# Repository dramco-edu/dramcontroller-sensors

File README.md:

# Dramcontroller Sensors
Description and hardware schemes for sensors compatible with dramcontroller boards

In academic year 2021-2022, students have access to six different sensor modules. 
- Button Sensor
- Capacitive Touch Sensor
- Sound Sensor
- Inertial Measurement Unit Sensor
- Digital Light Intensity Sensor
- Proximity Sensor

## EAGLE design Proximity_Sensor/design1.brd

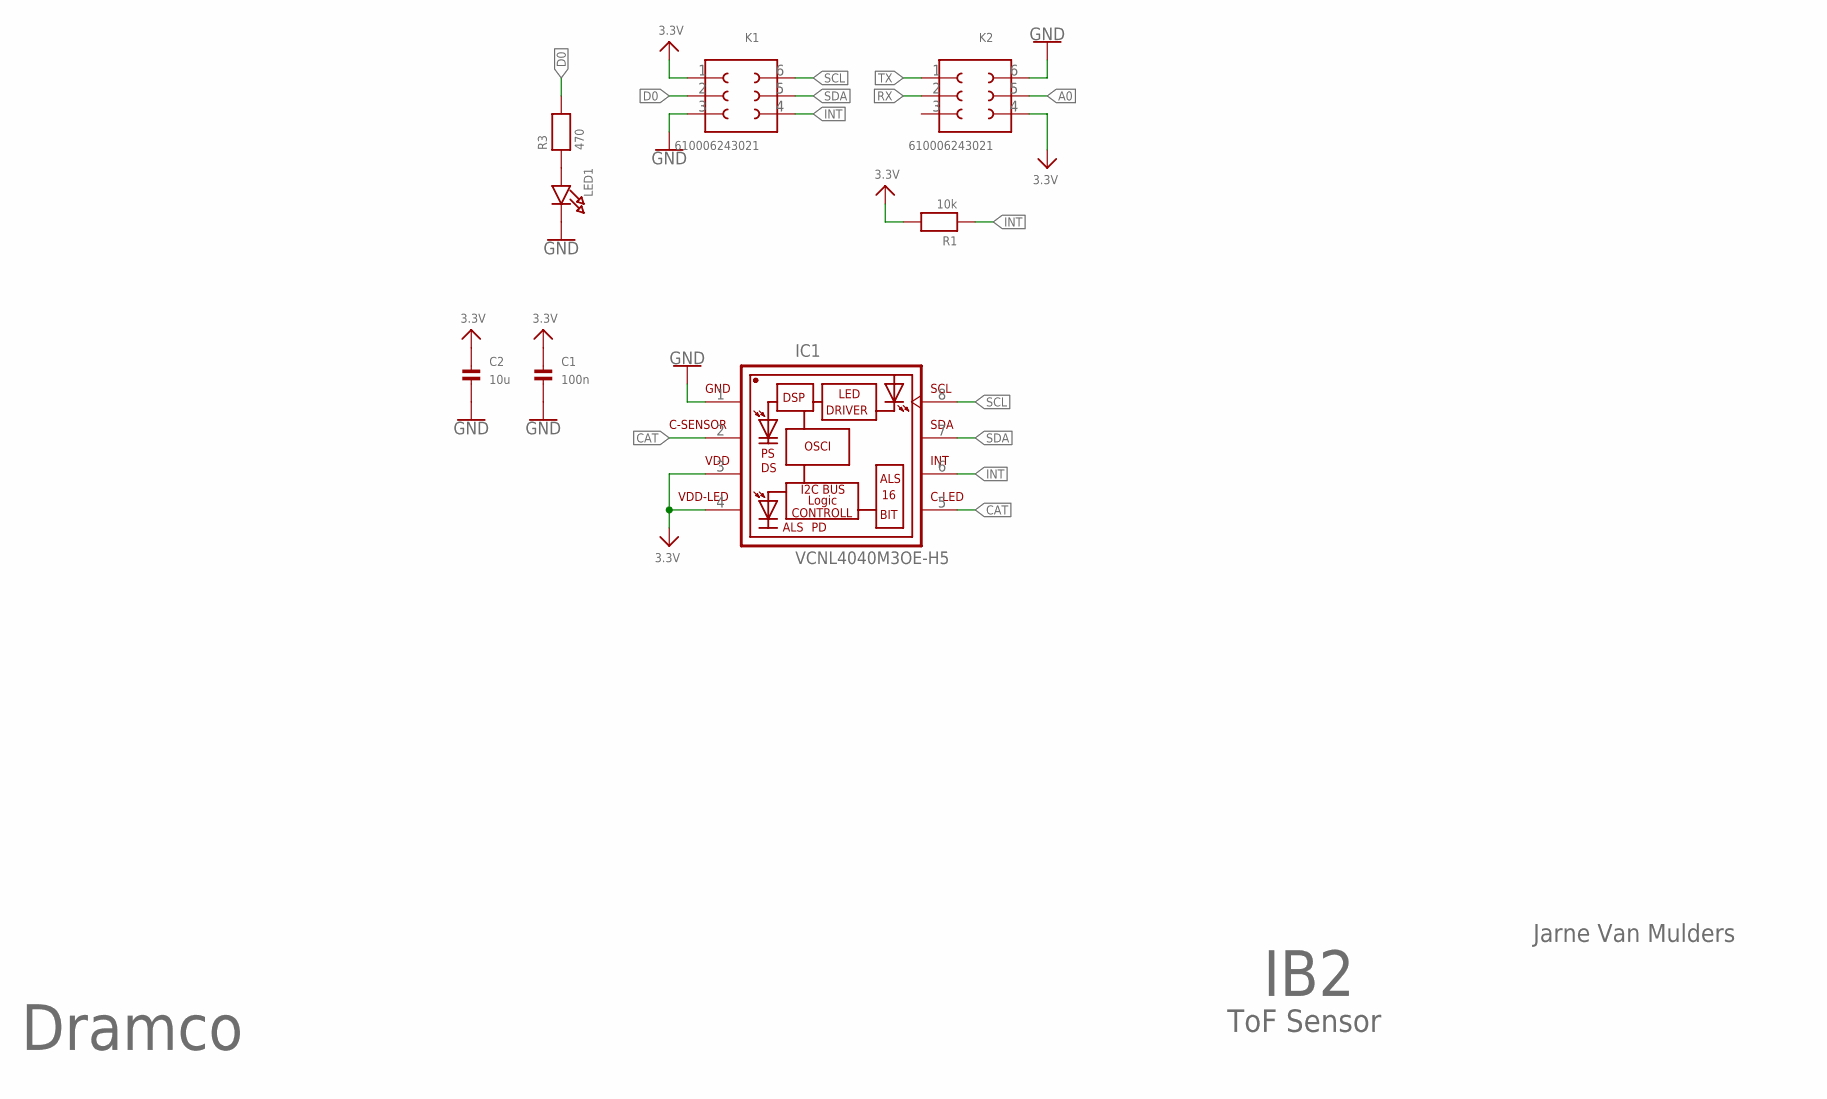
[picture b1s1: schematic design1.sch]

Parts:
C1: 100n; 0603
C2: 10u; 0805
IC1: VCNL4040M3OE-H5; VISHAY_VCNL4040_4.34X2.35X3.65
K1, K2: 610006243021
LED1: LED0805; CHIPLED_0805
R1: 10k; 0603
R3: 470; 0603

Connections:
3.3V: C1.1, C2.1, IC1.3 (VDD), IC1.4 (VDD-LED), K1.1, K2.4, R1.2
A0: K2.5
CAT: IC1.2 (C-SENSOR), IC1.5 (C-LED)
D0: K1.2, R3.2
GND: C1.2, C2.2, IC1.1 (GND), K1.3, K2.6, LED1.C
INT: IC1.6 (INT), K1.4, R1.1
unnamed: LED1.A, R3.1
RX: K2.2
SCL: IC1.8 (SCL), K1.6
SDA: IC1.7 (SDA), K1.5
TX: K2.1

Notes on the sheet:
Dramco
IB2
ToF Sensor
Jarne Van Mulders

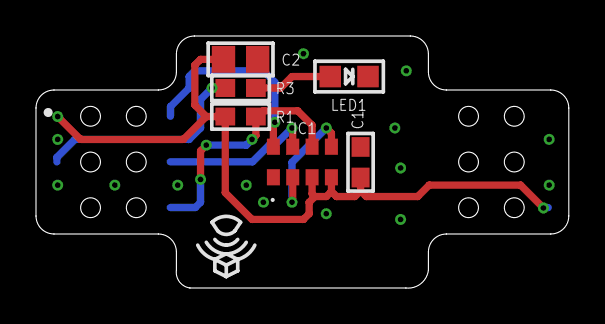
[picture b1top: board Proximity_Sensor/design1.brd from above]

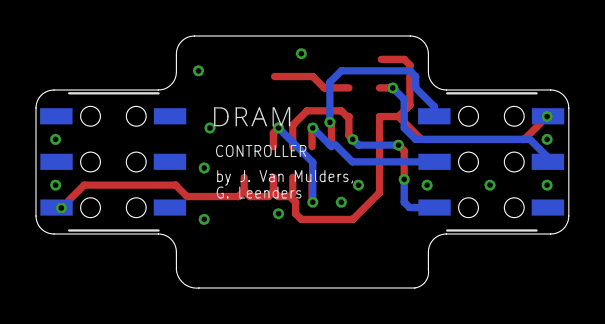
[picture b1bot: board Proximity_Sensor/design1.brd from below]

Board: 2 copper layers, 29.6 x 14.0 mm, 8 parts (2 on the bottom side), 8 nets.

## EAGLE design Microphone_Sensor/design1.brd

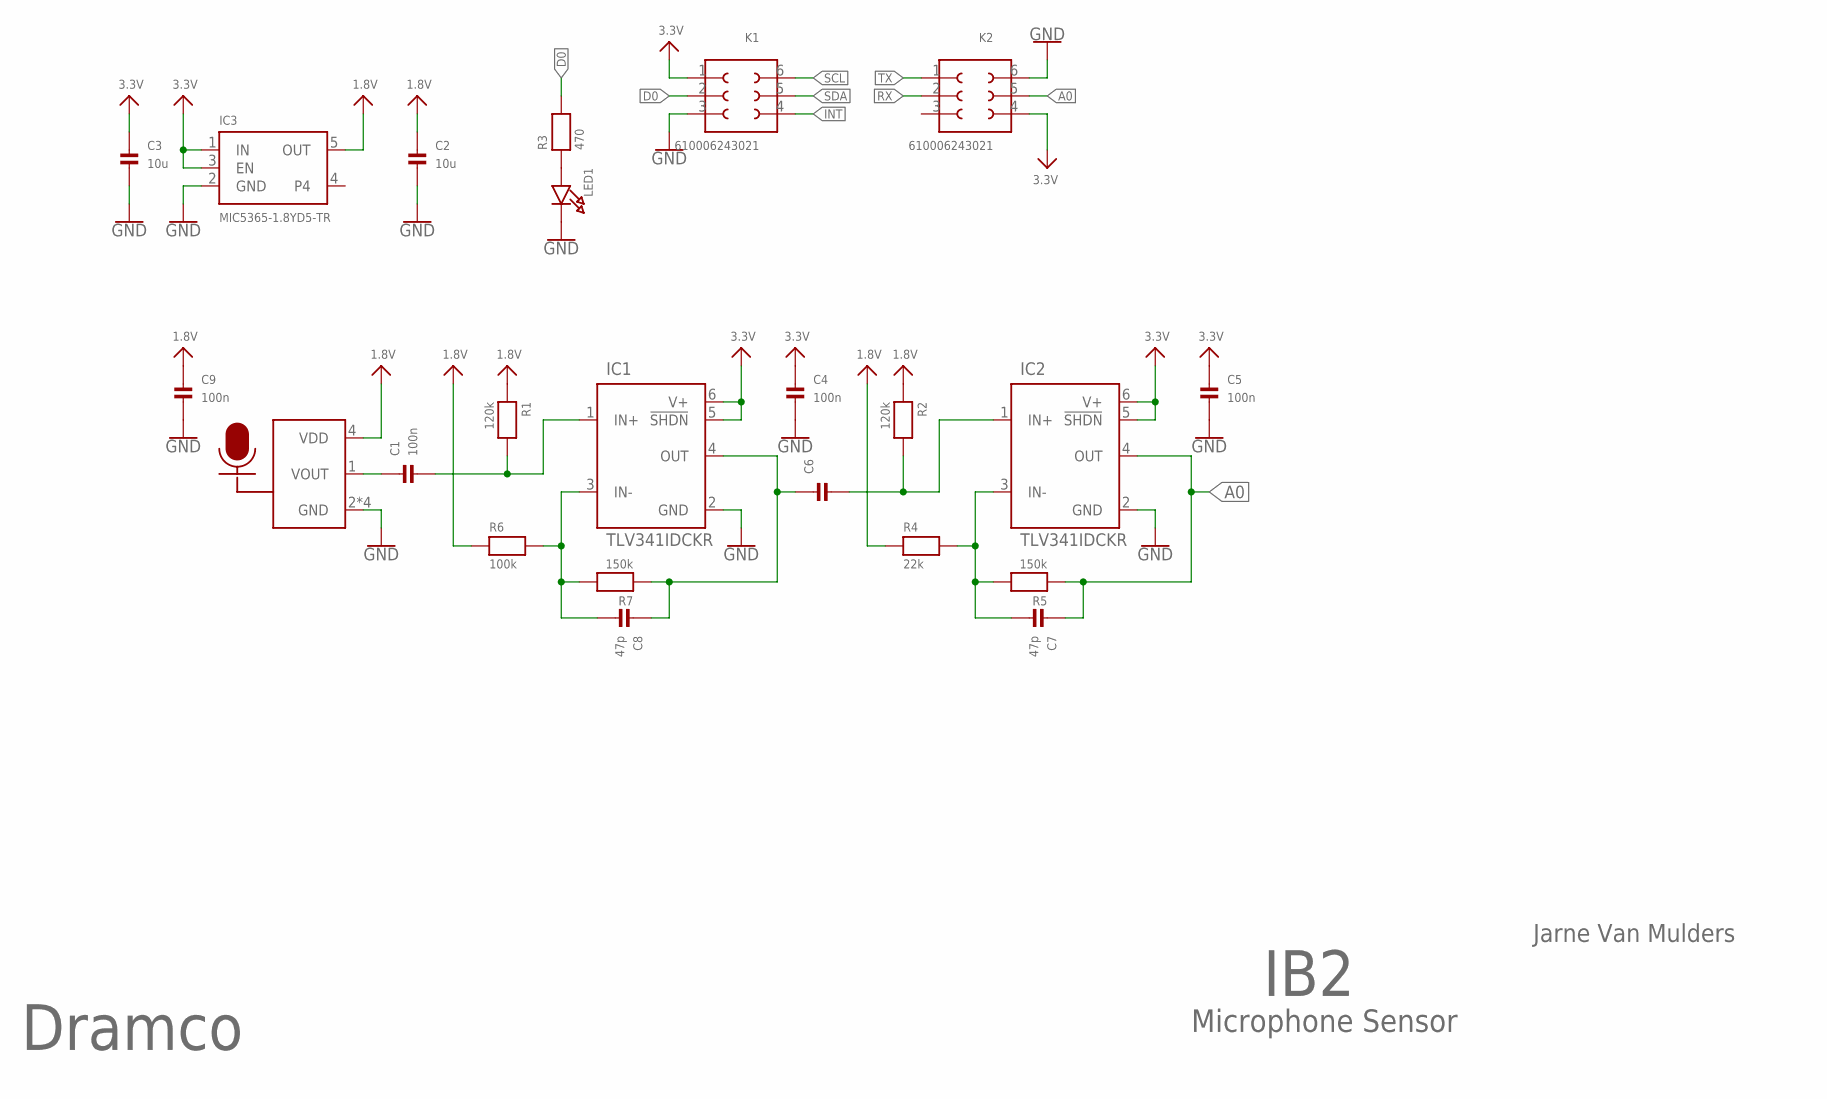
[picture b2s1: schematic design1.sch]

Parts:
C1, C4, C5, C9: 100n; 0603-MINI
C2, C3: 10u; 0603-MINI
C6: CAP_CERAMIC0603MINI; 0603-MINI
C7, C8: 47p; 0603-MINI
IC1, IC2: TLV341IDCKR; SOT65P210X110-6N
IC3: MIC5365-1.8YD5-TR; SOT23-5
IC4: VM1000
K1, K2: 610006243021
LED1: LED0805; CHIPLED_0805
R1, R2: 120k; 0603-MINI
R3: 470; 0603-MINI
R4: 22k; 0603-MINI
R5, R7: 150k; 0603-MINI
R6: 100k; 0603-MINI

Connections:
1.8V: C2.1, C9.1, IC3.5 (OUT), IC4.4 (VDD), R1.1, R2.1, R4.1, R6.1
3.3V: C3.1, C4.1, C5.1, IC1.5 (!SHDN!), IC1.6 (V+), IC2.5 (!SHDN!), IC2.6 (V+), IC3.1 (IN), IC3.3 (EN), K1.1, K2.4
A0: C7.1, IC2.4 (OUT), K2.5, R5.1
D0: K1.2, R3.2
GND: C2.2, C3.2, C4.2, C5.2, C9.2, IC1.2 (GND), IC2.2 (GND), IC3.2 (GND), IC4.2 (GND), IC4.3 (GND), IC4.5 (GND), IC4.6 (GND), K1.3, K2.6, LED1.C
INT: K1.4
unnamed: C1.1, IC4.1 (VOUT)
unnamed: C1.2, IC1.1 (IN+), R1.2
unnamed: LED1.A, R3.1
unnamed: C7.2, IC2.3 (IN-), R4.2, R5.2
unnamed: C6.1, C8.1, IC1.4 (OUT), R7.1
unnamed: C6.2, IC2.1 (IN+), R2.2
unnamed: C8.2, IC1.3 (IN-), R6.2, R7.2
RX: K2.2
SCL: K1.6
SDA: K1.5
TX: K2.1

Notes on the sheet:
Dramco
IB2
Microphone Sensor
Jarne Van Mulders

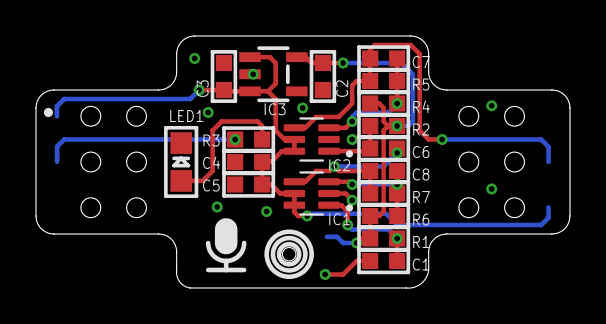
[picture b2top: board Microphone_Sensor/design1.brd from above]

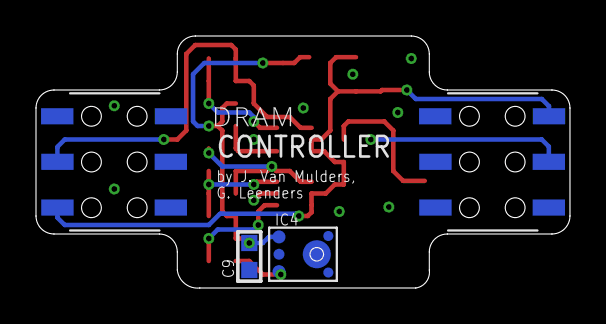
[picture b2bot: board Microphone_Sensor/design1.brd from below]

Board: 2 copper layers, 29.7 x 14.0 mm, 23 parts (4 on the bottom side), 12 nets.

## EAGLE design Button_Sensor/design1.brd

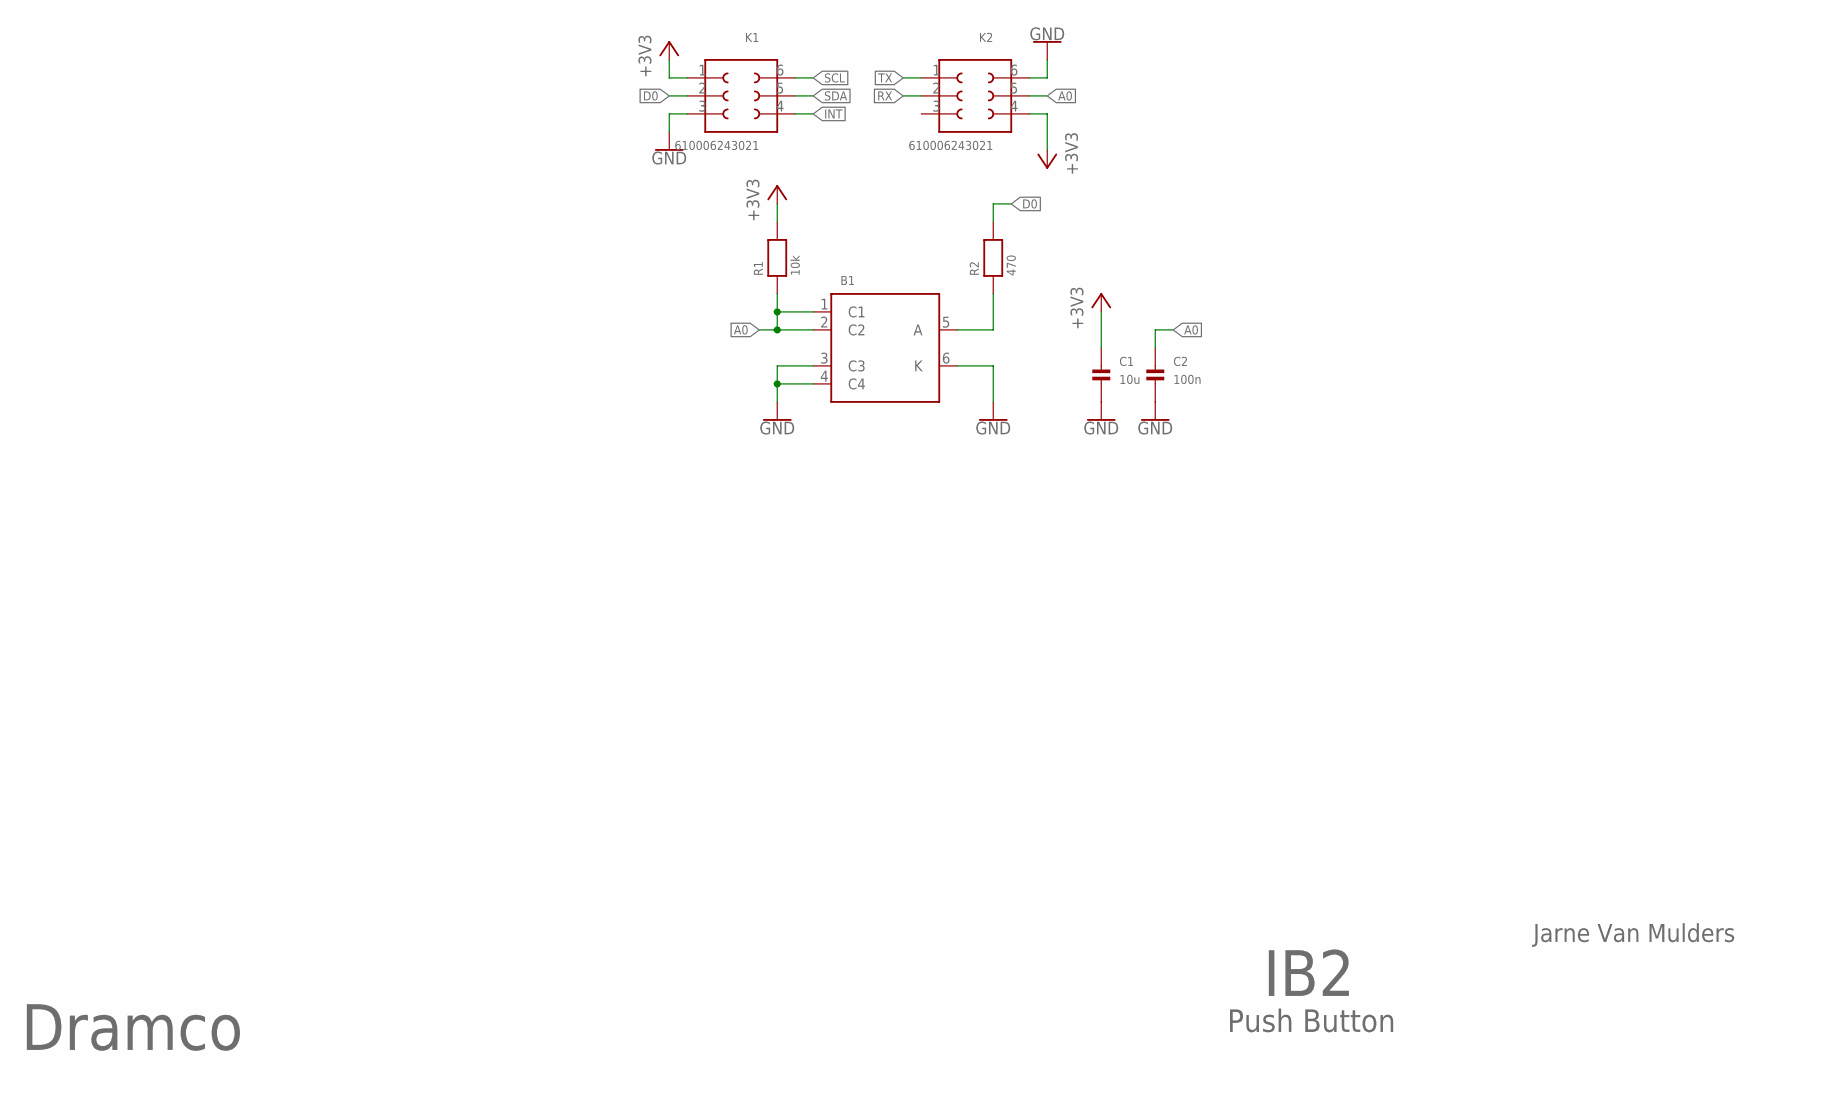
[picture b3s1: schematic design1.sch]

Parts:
B1: TS121273_AKSMD
C1: 10u; 0805
C2: 100n; 0603
K1, K2: 610006243021
R1: 10k; 0603
R2: 470; 0603

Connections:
+3V3: C1.1, K1.1, K2.4, R1.2
A0: B1.1 (C1), B1.2 (C2), C2.1, K2.5, R1.1
D0: K1.2, R2.2
GND: B1.3 (C3), B1.4 (C4), B1.6 (K), C1.2, C2.2, K1.3, K2.6
INT: K1.4
unnamed: B1.5 (A), R2.1
RX: K2.2
SCL: K1.6
SDA: K1.5
TX: K2.1

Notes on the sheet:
Dramco
IB2
Push Button
Jarne Van Mulders

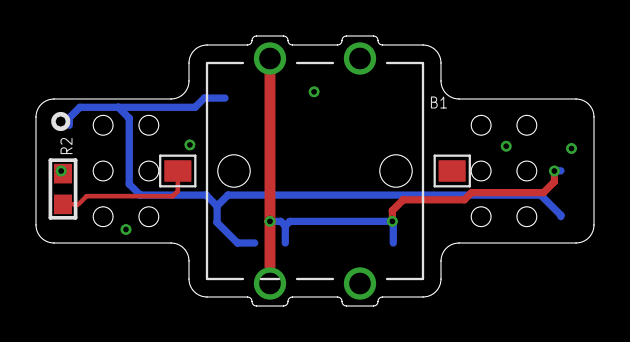
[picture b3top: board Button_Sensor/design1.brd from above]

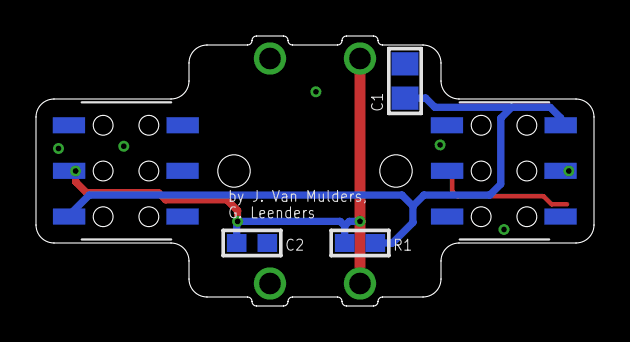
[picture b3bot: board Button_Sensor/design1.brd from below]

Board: 2 copper layers, 31.0 x 15.0 mm, 7 parts (5 on the bottom side), 5 nets.

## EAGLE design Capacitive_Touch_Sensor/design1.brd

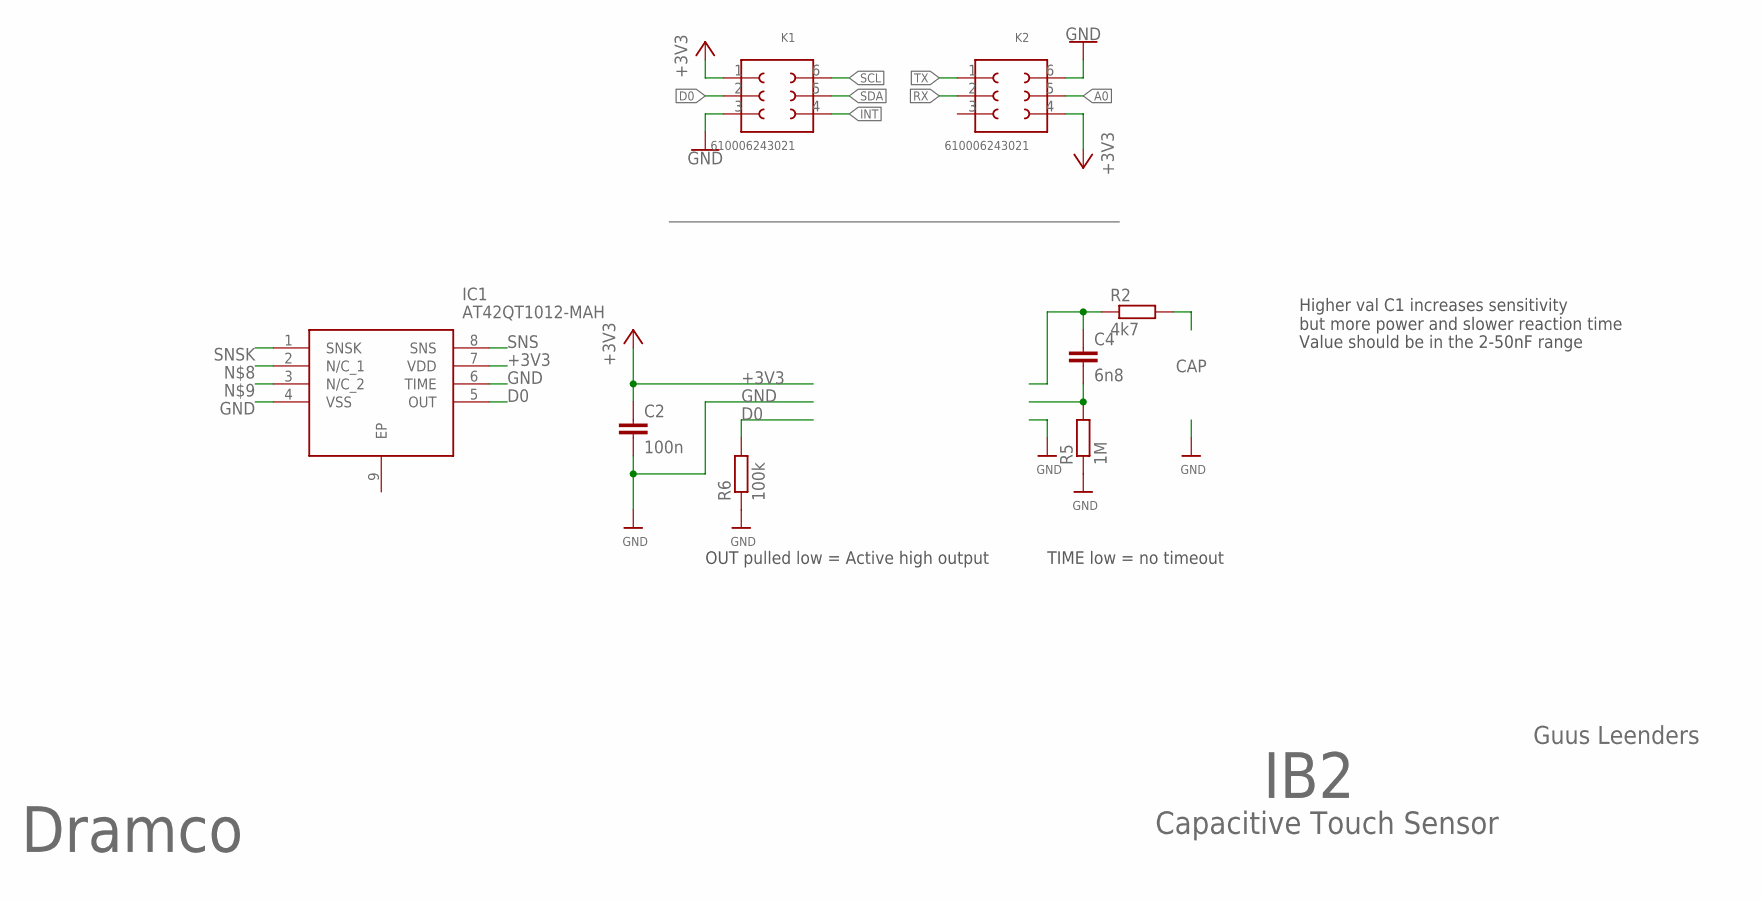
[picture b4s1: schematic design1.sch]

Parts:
C2: 100n; C0603
C4: 6n8; C0603
IC1: AT42QT1012-MAH; SON50P200X200X60-9N
K1, K2: 610006243021
R2: 4k7; R0603
R5: 1M; R0603
R6: 100k; R0603

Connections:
+3V3: C2.1, IC1.7 (VDD), K1.1, K2.4
A0: K2.5
D0: IC1.5 (OUT), K1.2, R6.2
GND: C2.2, IC1.4 (VSS), IC1.6 (TIME), K1.3, K2.6, R5.1, R6.1
INT: K1.4
RX: K2.2
SCL: K1.6
SDA: K1.5
SNS: C4.2, IC1.8 (SNS), R5.2
SNSK: C4.1, IC1.1 (SNSK), R2.1
TX: K2.1

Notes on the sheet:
Dramco
IB2
Capacitive Touch Sensor
Guus Leenders
Higher val C1 increases sensitivity but more power and slower reaction time
Value should be in the 2-50nF range
OUT pulled low = Active high output
TIME low = no timeout
CAP

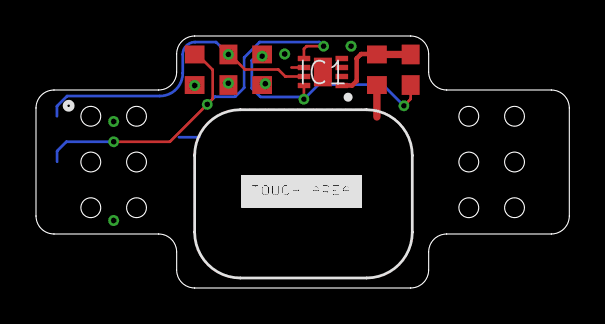
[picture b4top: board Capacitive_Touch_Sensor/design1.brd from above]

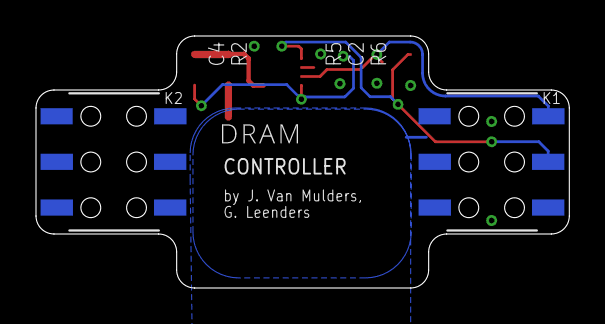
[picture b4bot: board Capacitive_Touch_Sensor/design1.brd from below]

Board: 2 copper layers, 29.6 x 14.0 mm, 8 parts (2 on the bottom side), 5 nets.

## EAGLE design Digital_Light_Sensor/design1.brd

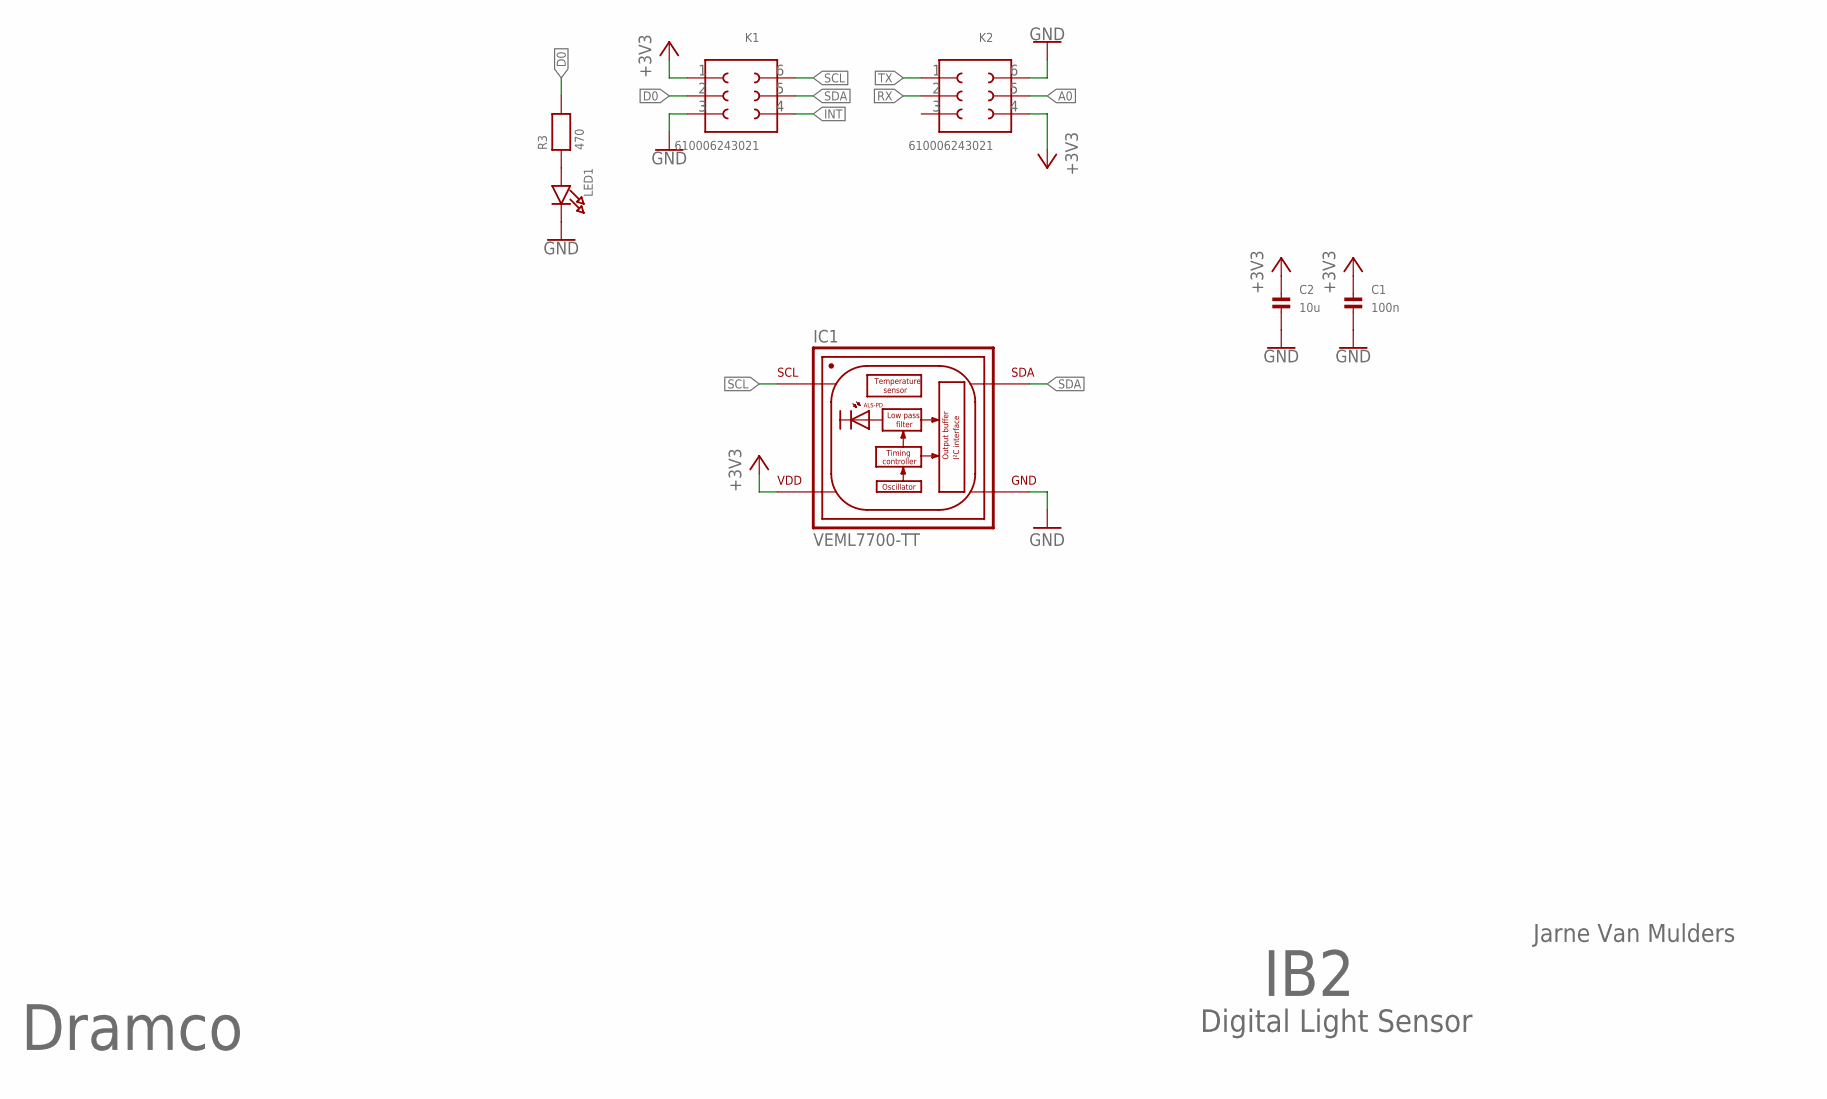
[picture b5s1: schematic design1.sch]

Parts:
C1: 100n; 0603
C2: 10u; 0805
IC1: VEML7700-TT; XDCR_VEML7700-TT
K1, K2: 610006243021
LED1: LED0805; CHIPLED_0805
R3: 470; 0603

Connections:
A0: K2.5
D0: K1.2, R3.2
GND: C1.2, C2.2, IC1.3 (GND), K1.3, K2.6, LED1.C
INT: K1.4
unnamed: LED1.A, R3.1
unnamed: C1.1, C2.1, IC1.2 (VDD), K1.1, K2.4
RX: K2.2
SCL: IC1.1 (SCL), K1.6
SDA: IC1.4 (SDA), K1.5
TX: K2.1

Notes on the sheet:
Dramco
IB2
Digital Light Sensor
Jarne Van Mulders

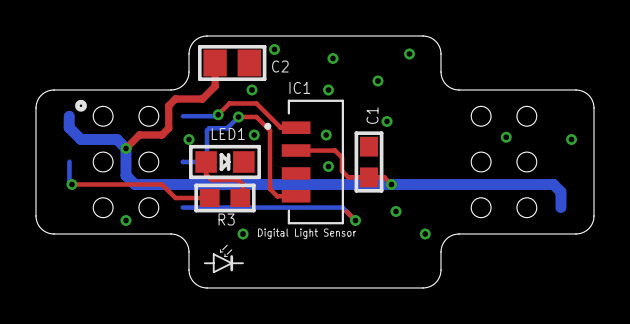
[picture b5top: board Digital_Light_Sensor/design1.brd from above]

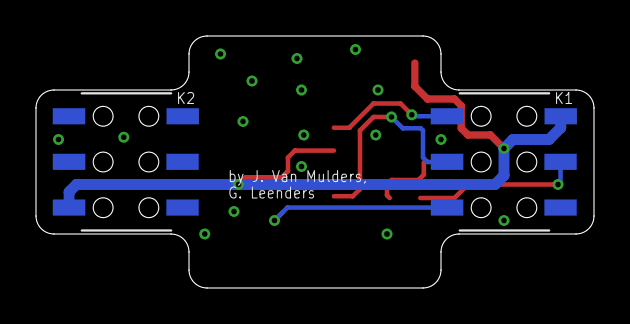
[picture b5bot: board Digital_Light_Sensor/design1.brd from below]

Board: 2 copper layers, 31.0 x 14.0 mm, 7 parts (2 on the bottom side), 6 nets.

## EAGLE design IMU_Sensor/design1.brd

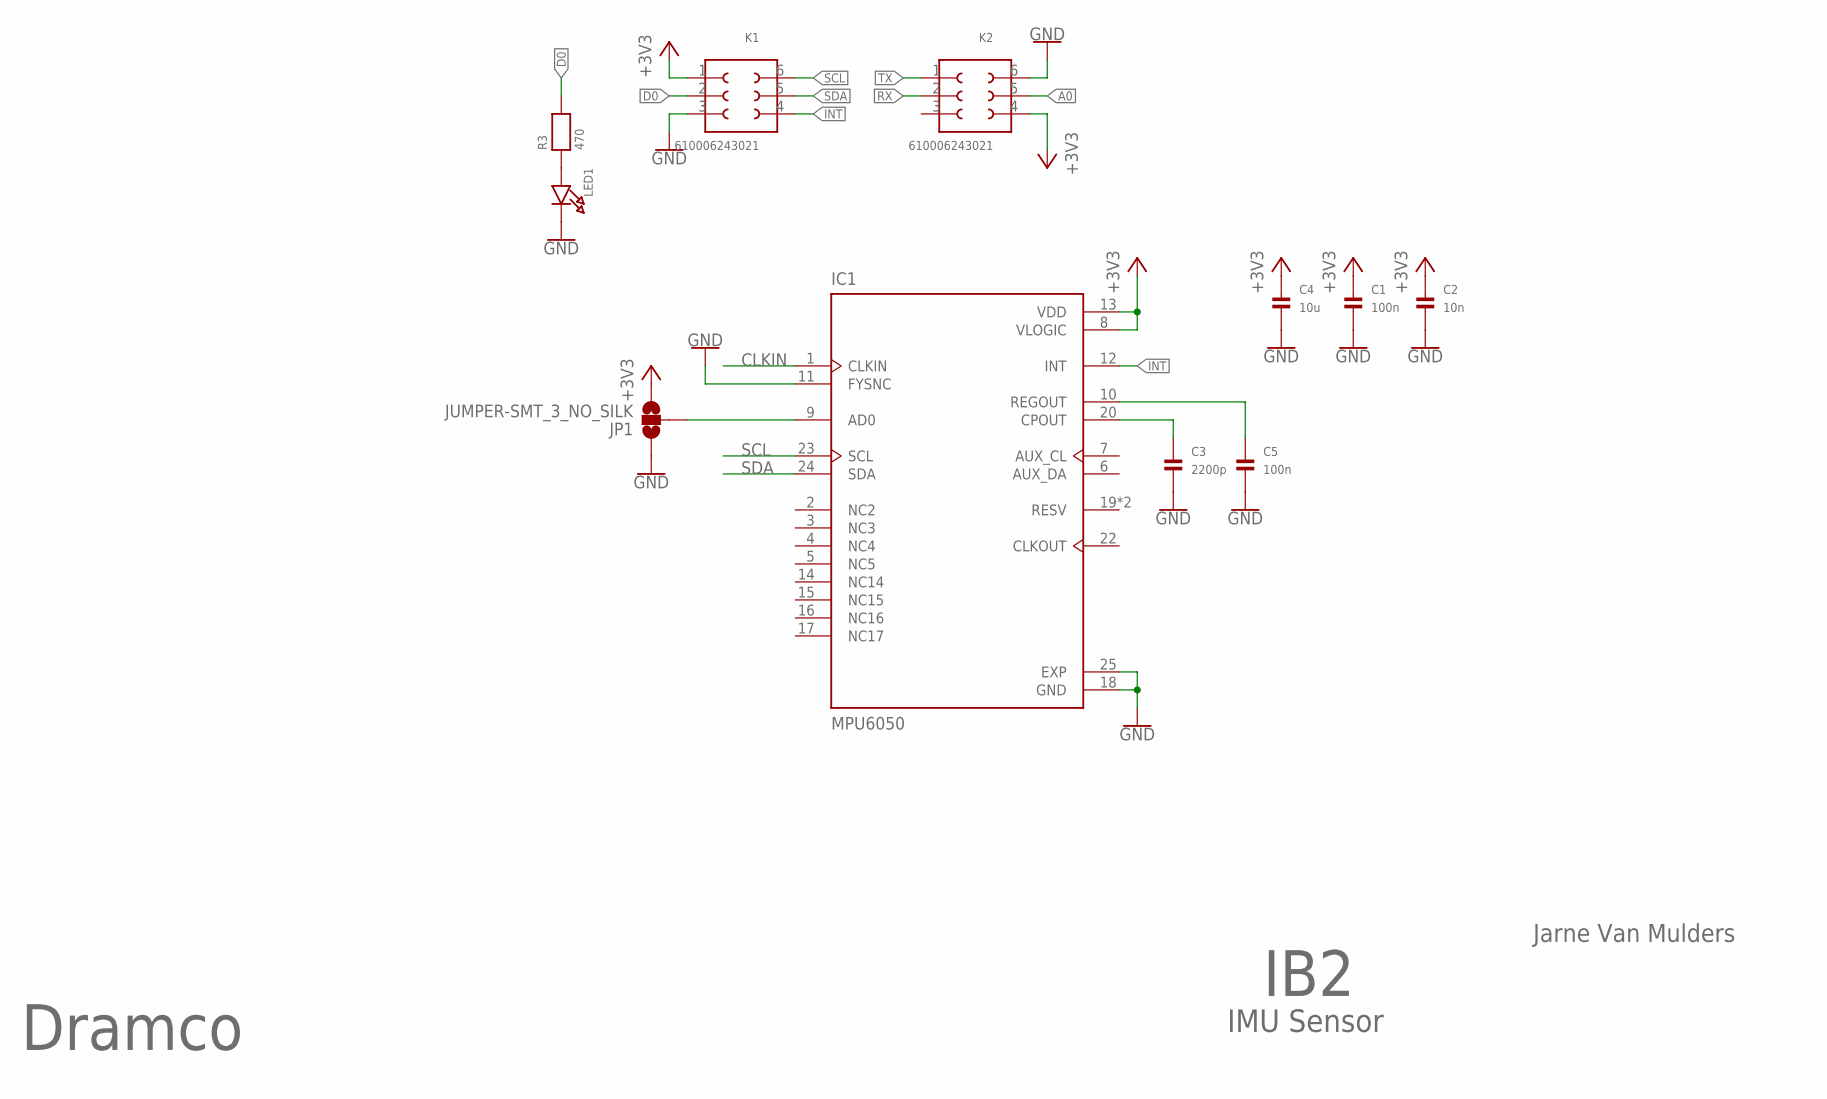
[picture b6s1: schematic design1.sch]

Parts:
C1, C5: 100n; 0603
C2: 10n; 0603
C3: 2200p; 0603
C4: 10u; 0805
IC1: MPU6050; IC_MPU6050
JP1: JUMPER-SMT_3_NO_SILK; SMT-JUMPER_3_NO_SILK
K1, K2: 610006243021
LED1: LED0805; CHIPLED_0805
R3: 470; 0603

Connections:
A0: K2.5
CLKIN: IC1.1 (CLKIN)
D0: K1.2, R3.2
GND: C1.2, C2.2, C3.2, C4.2, C5.2, IC1.11 (FYSNC), IC1.18 (GND), IC1.25 (EXP), JP1.1, K1.3, K2.6, LED1.C
INT: IC1.12 (INT), K1.4
unnamed: C3.1, IC1.20 (CPOUT)
unnamed: C5.1, IC1.10 (REGOUT)
unnamed: LED1.A, R3.1
unnamed: IC1.9 (AD0), JP1.2
unnamed: C1.1, C2.1, C4.1, IC1.8 (VLOGIC), IC1.13 (VDD), JP1.3, K1.1, K2.4
RX: K2.2
SCL: IC1.23 (SCL), K1.6
SDA: IC1.24 (SDA), K1.5
TX: K2.1

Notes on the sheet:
Dramco
IB2
IMU Sensor
Jarne Van Mulders

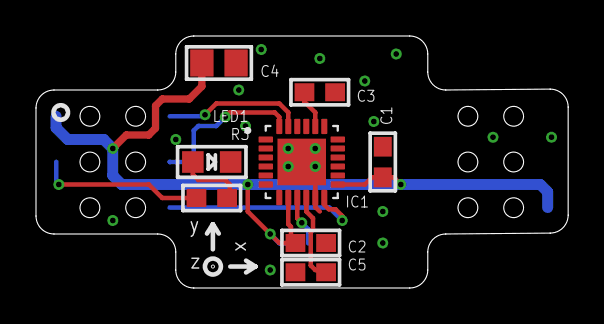
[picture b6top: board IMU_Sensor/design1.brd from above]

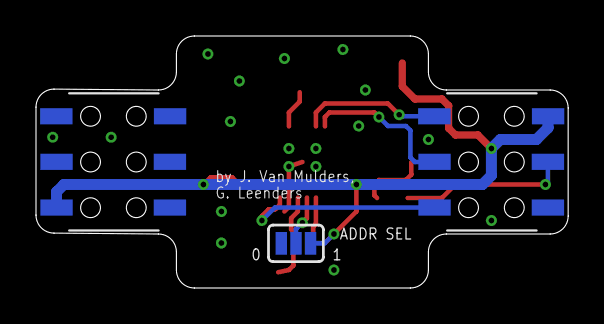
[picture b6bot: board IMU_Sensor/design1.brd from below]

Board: 2 copper layers, 29.6 x 14.0 mm, 11 parts (3 on the bottom side), 10 nets.

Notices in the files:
parts and their libraries:
microbuilder: This work is placed in the public domain, and may be freely used for commercial and non-commercial work with the following conditions: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
Wurth_Elektronik_Electromechanic_Board_t: Copyright: Würth Elektronik
